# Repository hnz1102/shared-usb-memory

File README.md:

<div align="center">
  <h1><code>SHARED-USB-MEMORY</code></h1>
  
</div>

# Shared USB Memory : USB Memory with One-touch Switching Between Two Device Connections

https://github.com/hnz1102/shared-usb-memory/assets/111413646/2c444520-a98f-45e1-a0ac-f0b2667a8621

This memory provides convenient and quick-to-switch connections between two host devices such as PCs.

When the network is not available, data is transferred by copying data to and from a USB memory stick or SD card. However, since removing and inserting USB memory sticks and SD cards is a hassle, the Box can be switched at the touch of a button to pass data back and forth.

To use, connect this Box between two PCs with a Type-C cable. The disk will be recognized by the PC connected to the left port. Then, copy data here, and when the red access blinking stops, press the red button. Then the disk will be recognized in the PC of right port and you can retrieve the data. Press the red button again to return the disk to the left PC. In this way, data can be exchanged without having to remove and insert the USB memory stick.

The box can be run on the Windows OS, MacOS, and Linux OS without special drivers.

## Schematic

This Board Schematic and a PCB layout are placed in this directory. 
Schematic data is created by KidCad 7.0.
The PCB was manufuctured by [PCBWay](https://www.pcbway.com/). I could easily order my custom boards to the PCBWay.
Click online order [page](https://www.pcbway.com/QuickOrderOnline.aspx), then clink the "Add Gerber File" button, you can upload the [gerber file](https://github.com/hnz1102/shared-usb-memory/raw/main/shareusbdisk2.kicad_pcb.zip).

When ordering the PCB, the parameters can be almost default values, but "Min hole size" should be 0.25mm and "Immersion gold (ENIG)" should be selected for "Surface finish". The reason for this is that the minimum Via Hole is 0.25mm, and if the eMMC pad is not "Immersion gold (ENIG)", the solder on the pad will be slightly raised and cannot be soldered properly without misalignment.

After assembling the board, It has to configure EEPROMs of the USB Media Controller.

The USB Media Controller has an EEPROM. It is programmed with the parameters by [USBDM tool](https://www.microchip.com/en-us/software-library/usbdm-tool).

- Manufacture String
- Serial Number String

This board has two USB Media Controller. Connect to each of the two respective USB ports and rewrite the information with the USBDM tool. 

# Container

There are STL data for 3D printer in the `stl` directory.

## LICENSE
Hardware Schematic Documents are licensed under CC-BY-SA V4.0.

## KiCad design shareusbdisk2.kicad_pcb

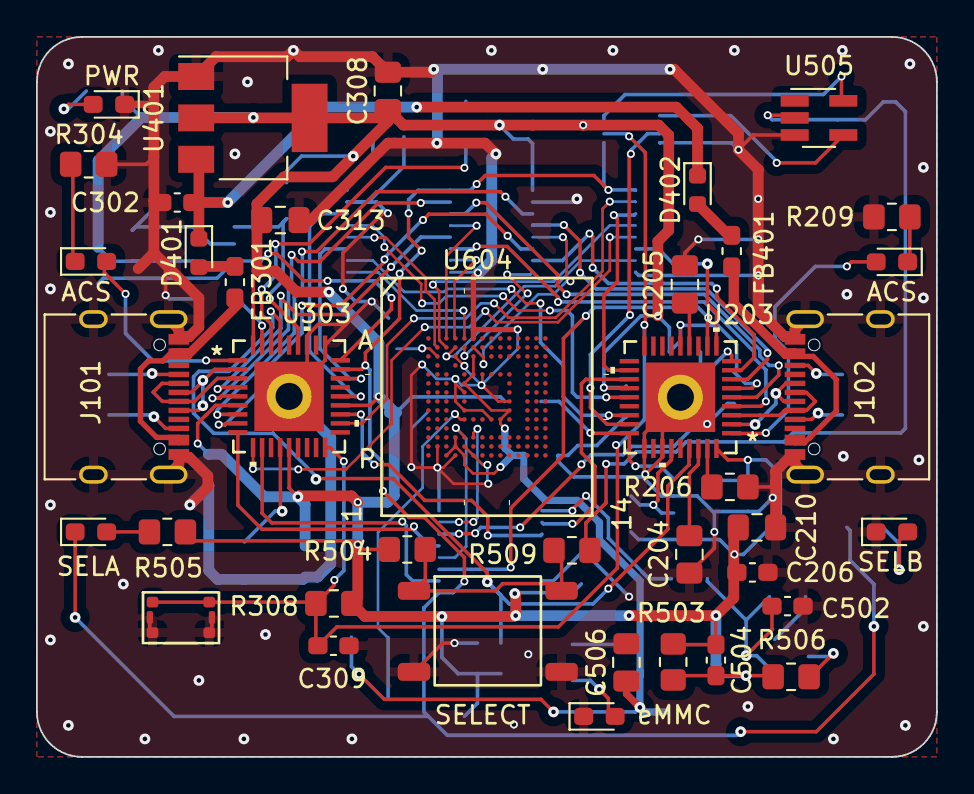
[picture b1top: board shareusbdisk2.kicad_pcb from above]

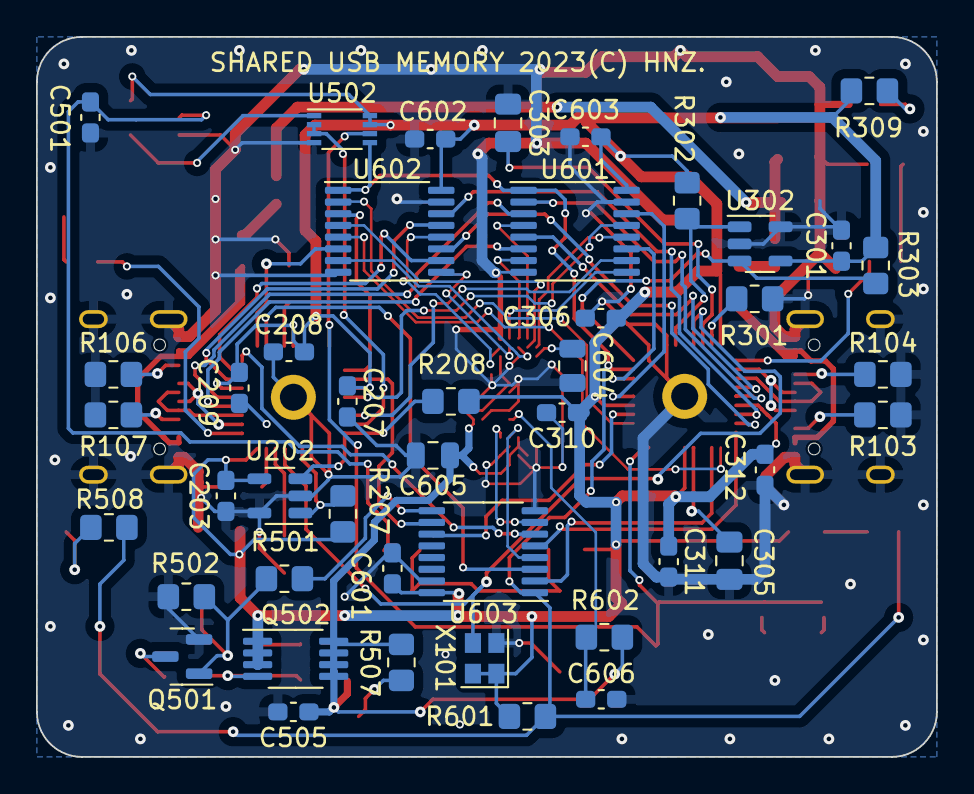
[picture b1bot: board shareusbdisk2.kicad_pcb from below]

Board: 2 copper layers, 50.0 x 40.0 mm, 83 parts (44 on the bottom side), 79 nets.

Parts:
C203, C206, C207, C208, C209, C301, C302, C306, C309, C310, C311, C312, C501, C502, C505, C601, C602, C603, C606: 0.1uF; C_0603_1608Metric_Pad1.08x0.95mm_HandSolder
C204, C205, C303, C305: 1uF; C_0805_2012Metric_Pad1.18x1.45mm_HandSolder
C210, C313: 4.7uF; C_0805_2012Metric_Pad1.18x1.45mm_HandSolder
C308, C506: 10uF; C_0805_2012Metric_Pad1.18x1.45mm_HandSolder
C504: 2.2uF; C_0603_1608Metric_Pad1.08x0.95mm_HandSolder
C604, C605: 1uF; C_0805_2012Metric
D203, D301, D302: LED RED; LED_0603_1608Metric_Pad1.05x0.95mm_HandSolder
D401, D402: CDBU0520-HF; D_0603_1608Metric
D501: eMMC PWR LED RED; LED_0603_1608Metric_Pad1.05x0.95mm_HandSolder
D502: SEL_A; LED_0603_1608Metric_Pad1.05x0.95mm_HandSolder
D503: SEL_B; LED_0603_1608Metric_Pad1.05x0.95mm_HandSolder
FB301, FB401: BK2125HS601-T; L_0603_1608Metric_Pad1.05x0.95mm_HandSolder
J101, J102: USB_C_Receptacle_USB2.0_5077CR; USB_C_5077CR-16-SMC2-BK-TR
Q501: 2N7002K; SOT-23
Q502: IRF7606TRPBF; MSOP-8_3x3mm_P0.65mm
R103, R104, R106, R107: 5.1K; R_0805_2012Metric_Pad1.20x1.40mm_HandSolder
R206, R301: 12K 1%; R_0805_2012Metric_Pad1.20x1.40mm_HandSolder
R207, R208, R302, R303, R308, R502, R503, R504, R601, R602: 10K; R_0805_2012Metric_Pad1.20x1.40mm_HandSolder
R209, R304: 330R; R_0805_2012Metric_Pad1.20x1.40mm_HandSolder
R309, R506, R507, R509: 1K; R_0805_2012Metric_Pad1.20x1.40mm_HandSolder
R501: 2K; R_0805_2012Metric_Pad1.20x1.40mm_HandSolder
R505, R508: 330; R_0805_2012Metric_Pad1.20x1.40mm_HandSolder
SW301: RESET SW; WS-TASV SMT Tact Switch
SW501: TS-06104
U202, U302: AT24C04-STUM; SOT-23-5
U203, U303: USB2244-AEZG-06; QFN36_6X6MC_MCH
U401: LD1117S33TR_SOT223; SOT-223-3_TabPin2
U502: 74LVC2G74; VSSOP-8_2.3x2mm_P0.5mm
U505: 74AHC1G14; SOT-23-5_HandSoldering
U601, U602, U603: TMUX1574PWR; TSSOP-16_4.4x5mm_P0.65mm
U604: EM32VSUKN; EM32VSUKN FPGA153
X101: SG-210STF 24MHz; Oscillator_SMD_SeikoEpson_SG210-4Pin_2.5x2.0mm

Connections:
+3.3V: C203.1, C206.1, C207.1, C208.1, C209.1, C210.1, C301.1, C306.1, C308.1, C310.1, C311.1, C312.1, C313.1, C504.1, C601.1, C602.1, C603.1, Q502.1 (S), Q502.2 (S), Q502.3 (S), R207.1, R208.1, R302.1, R303.1, R308.1, R309.1, R503.1, R504.1, R505.1, R601.1, U202.4 (VCC), U203.6 (VDD33), U203.14 (VDD33), U203.22 (VDD33), U203.36 (VDDA33), U302.4 (VCC), U303.6 (VDD33), U303.14 (VDD33), U303.22 (VDD33), U303.36 (VDDA33), U401.2 (VO), U502.7 (~PRE), U502.8 (VCC), U505.5 (VCC), U601.16 (VDD), U602.16 (VDD), U603.16 (VDD), X101.1 (~ST), X101.4 (Vcc)
+5V: C302.1, D401.1 (K), D402.1 (K), U401.3 (VI)
/MUX/CLK: U603.7 (D2), U604.M6 (CLK)
/MUX/CMD: U603.4 (D1), U604.M5 (CMD)
/MUX/CRD_PWR_A: U303.21 (CRD_PWR), U603.11 (S3A)
/MUX/CRD_PWR_B: U203.21 (CRD_PWR), U603.10 (S3B)
/MUX/D0: U601.4 (D1), U604.A3 (DAT0)
/MUX/D1: U601.7 (D2), U604.A4 (DAT1)
/MUX/D2: U601.9 (D3), U604.A5 (DAT2)
/MUX/D3: U601.12 (D4), U604.B2 (DAT3)
/MUX/D4: U602.4 (D1), U604.B3 (DAT4)
/MUX/D5: U602.7 (D2), U604.B4 (DAT5)
/MUX/D6: U602.9 (D3), U604.B5 (DAT6)
/MUX/D7: U602.12 (D4), U604.B6 (DAT7)
/MUX/MMCDA0: U303.5 (SD_D0), U601.2 (S1A)
/MUX/MMCDA1: U303.4 (SD_D1), U601.5 (S2A)
/MUX/MMCDA2: U303.25 (SD_D2), U601.11 (S3A)
/MUX/MMCDA3: U303.23 (SD_D3), U601.14 (S4A)
/MUX/MMCDA4: U303.20 (SD_D4), U602.2 (S1A)
/MUX/MMCDA5: U303.10 (SD_D5), U602.5 (S2A)
/MUX/MMCDA6: U303.8 (SD_D6), U602.11 (S3A)
/MUX/MMCDA7: U303.7 (SD_D7), U602.14 (S4A)
/MUX/MMCDB0: U203.5 (SD_D0), U601.3 (S1B)
/MUX/MMCDB1: U203.4 (SD_D1), U601.6 (S2B)
/MUX/MMCDB2: U203.25 (SD_D2), U601.10 (S3B)
/MUX/MMCDB3: U203.23 (SD_D3), U601.13 (S4B)
/MUX/MMCDB4: U203.20 (SD_D4), U602.3 (S1B)
/MUX/MMCDB5: U203.10 (SD_D5), U602.6 (S2B)
/MUX/MMCDB6: U203.8 (SD_D6), U602.10 (S3B)
/MUX/MMCDB7: U203.7 (SD_D7), U602.13 (S4B)
/MUX/MMC_CLK_A: U303.9 (SD_CLK), U603.5 (S2A)
/MUX/MMC_CLK_B: U203.9 (SD_CLK), U603.6 (S2B)
/MUX/MMC_CMD_A: U303.11 (SD_CMD), U603.2 (S1A)
/MUX/MMC_CMD_B: U203.11 (SD_CMD), U603.3 (S1B)
/MUX/MMC_PWR: C505.1, C506.1, C605.1, Q502.5 (D), Q502.6 (D), Q502.7 (D), Q502.8 (D), R507.1, R602.1, U604.C6 (VCCQ), U604.E6 (VCC), U604.F5 (VCC), U604.J10 (VCC), U604.K9 (VCC), U604.M4 (VCCQ), U604.N4 (VCCQ), U604.P3 (VCCQ), U604.P5 (VCCQ)
/MUX/MMC_PWR_EN: R501.1, U603.9 (D3)
/MUX/~SELA: D502.1 (K), R508.1, R601.2, U303.26 (SD_NCD), U502.5 (Q), U601.1 (SEL), U602.1 (SEL), U603.1 (SEL)
/SDCARD_READER1/ACS: D203.2 (A), U203.1 (LED)
/SDCARD_READER1/CLK24MHZ: U203.33 (XTAL1(CLKIN)), U303.33 (XTAL1(CLKIN)), X101.3 (OUT)
/SDCARD_READER1/SCL: R207.2, U202.1 (SCL), U203.31 (TXD/SCK)
/SDCARD_READER1/SDA: R208.2, U202.3 (SDA), U203.27 (RXD/SDA)
/SDCARD_READER1/USB+: J102.A6 (D+), J102.B6 (D+), U203.2 (USB+)
/SDCARD_READER1/USB-: J102.A7 (D-), J102.B7 (D-), U203.3 (USB-)
/SDCARD_READER1/~MMC_CD: U203.26 (SD_NCD), U502.2 (D), U502.3 (~Q)
/SDCARD_READER1/~RESET: C309.1, R308.2, SW301.1, SW301.2, U203.18 (RESET_N), U303.18 (RESET_N), U502.6 (~CLR)
/SDCARD_READER2/ACS: D301.2 (A), U303.1 (LED)
/SDCARD_READER2/SCL: R302.2, U302.1 (SCL), U303.31 (TXD/SCK)
/SDCARD_READER2/SDA: R303.2, U302.3 (SDA), U303.27 (RXD/SDA)
/SDCARD_READER2/USB+: J101.A6 (D+), J101.B6 (D+), U303.2 (USB+)
/SDCARD_READER2/USB-: J101.A7 (D-), J101.B7 (D-), U303.3 (USB-)
/USB POWER/USBVDD_5V_A: FB301.1, J101.A4 (VBUS), J101.A9 (VBUS), J101.B4 (VBUS), J101.B9 (VBUS)
/USB POWER/USBVDD_5V_B: FB401.1, J102.A4 (VBUS), J102.A9 (VBUS), J102.B4 (VBUS), J102.B9 (VBUS)
GND: C203.2, C204.2, C205.2, C206.2, C207.2, C208.2, C209.2, C210.2, C301.2, C302.2, C303.2, C305.2, C306.2, C308.2, C309.2, C310.2, C311.2, C312.2, C313.2, C501.2, C502.2, C505.2, C506.2, C601.2, C602.2, C603.2, C604.2, C605.2, C606.2, D302.1 (K), D501.1 (K), D503.1 (K), J101.A1 (GND), J101.A12 (GND), J101.B1 (GND), J101.B12 (GND), J101.S1 (SHIELD), J102.A1 (GND), J102.A12 (GND), J102.B1 (GND), J102.B12 (GND), J102.S1 (SHIELD), Q501.2 (S), R103.2, R104.2, R106.2, R107.2, R206.2, R209.2, R301.2, R304.2, R502.2, SW301.3 (K), SW301.4 (A), SW301.5, SW301.6, SW501.A, SW501.B, U202.2 (GND), U202.5 (WP), U203.28 (TEST), U203.30 (SD_WP), U203.37 (EPAD), U302.2 (GND), U302.5 (WP), U303.28 (TEST), U303.30 (SD_WP), U303.37 (EPAD), U401.1 (GND), U502.4 (GND), U505.3 (GND), U601.8 (GND), U601.15 (~EN), U602.8 (GND), U602.15 (~EN), U603.8 (GND), U603.15 (~EN), U604.A6 (VSS), U604.C4 (VSSQ), U604.E7 (VSS), U604.G5 (VSS), U604.H10 (VSS), U604.J5 (VSS), U604.K8 (VSS), U604.N2 (VSSQ), U604.N5 (VSSQ), U604.P4 (VSSQ), U604.P6 (VSSQ), X101.2 (GND)
unnamed: C501.1, R509.1, U505.2
unnamed: D203.1 (K), R209.1
unnamed: D301.1 (K), R304.1
unnamed: D302.2 (A), R309.2
unnamed: D401.2 (A), FB301.2
unnamed: D402.2 (A), FB401.2
unnamed: D501.2 (A), R507.2
unnamed: D502.2 (A), R505.2
unnamed: D503.2 (A), R508.2
unnamed: J101.A5 (CC1), R104.1
unnamed: J101.B5 (CC2), R103.1
unnamed: J102.A5 (CC1), R107.1
unnamed: J102.B5 (CC2), R106.1
unnamed: Q501.3 (D), R506.1
unnamed: C502.1, Q501.1 (G), R501.2, R502.1
unnamed: C504.2, Q502.4 (G), R503.2, R506.2
unnamed: R504.2, R509.2, SW501.C, SW501.D
unnamed: R206.1, U203.35 (RBIAS)
unnamed: C205.1, U203.13 (VDD18)
unnamed: C204.1, U203.34 (VDD18PLL)
unnamed: R301.1, U303.35 (RBIAS)
unnamed: C305.1, U303.13 (VDD18)
unnamed: C303.1, U303.34 (VDD18PLL)
unnamed: U502.1 (C), U505.4
unnamed: C604.1, U604.C2 (VDDI)
unnamed: C606.1, R602.2, U604.K5 (~RST)

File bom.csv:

Reference,Value,Footprint,Datasheet,digikey,storeURL,Qty
"C206-C209,  C301, C302, C306, C309-C312, C501,  C502,  C505, C601-C603,  C606",0.1uF,Capacitor_SMD:C_0603_1608Metric_Pad1.08x0.95mm_HandSolder,~,311-1824-1-ND,https://www.digikey.com/en/products/detail/yageo/CC0603MRX7R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,19
"C204, C205, C303, C305",1uF,tbctl:C_0805_2012Metric_Pad1.18x1.45mm_HandSolder,~,13-CC0603KPX7R7BB105CT-ND,https://www.digikey.com/en/products/detail/yageo/CC0603KPX7R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,4
"C210, C313",4.7uF,tbctl:C_0805_2012Metric_Pad1.18x1.45mm_HandSolder,~,311-1455-1-ND,https://www.digikey.com/en/products/detail/yageo/CC0603KRX5R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,2
"C308, C506",10uF,Capacitor_SMD:C_0805_2012Metric_Pad1.18x1.45mm_HandSolder,~,311-3494-1-ND,https://www.digikey.com/en/products/detail/yageo/CC0603MRX5R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,2
C504,2.2uF,Capacitor_SMD:C_0603_1608Metric_Pad1.08x0.95mm_HandSolder,~,311-1795-1-ND,https://www.digikey.com/en/products/detail/yageo/CC0603KRX7R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,1
"C604, C605",1uF,Capacitor_SMD:C_0805_2012Metric,~,13-CC0603KPX7R7BB105CT-ND,https://www.digikey.com/en/products/detail/yageo/CC0603KPX7R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,2
"D203, D301, D302",LED RED,tbctl:LED_0603_1608Metric_Pad1.05x0.95mm_HandSolder,~,511-1587-1-ND,https://www.digikey.com/en/products/detail/rohm-semiconducto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,3
"D401, D402",CDBU0520-HF,Diode_SMD:D_0603_1608Metric,https://www.comchiptech.com/admin/files/product/QW-G1012-CDB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,641-2022-1-ND,https://www.digikey.com/en/products/detail/comchip-technolog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,2
D501,eMMC PWR LED RED,tbctl:LED_0603_1608Metric_Pad1.05x0.95mm_HandSolder,~,511-1587-1-ND,https://www.digikey.com/en/products/detail/rohm-semiconducto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,1
D502,SEL_A,tbctl:LED_0603_1608Metric_Pad1.05x0.95mm_HandSolder,~,846-1177-1-ND,https://www.digikey.com/en/products/detail/rohm-semiconducto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,1
D503,SEL_B,tbctl:LED_0603_1608Metric_Pad1.05x0.95mm_HandSolder,~,846-1177-1-ND,https://www.digikey.com/en/products/detail/rohm-semiconducto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,1
"FB301, FB401",BK2125HS601-T,tbctl:L_0603_1608Metric_Pad1.05x0.95mm_HandSolder,~,240-2399-1-ND ,https://www.digikey.com/en/products/detail/laird-signal-inte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,2
"J101, J102",USB_C_Receptacle_USB2.0_5077CR,tbctl:USB_C_5077CR-16-SMC2-BK-TR,https://www.usb.org/sites/default/files/documents/usb_type-c.zip,2073-USB4105-GF-ACT-ND,https://www.digikey.com/en/products/detail/gct/USB4105-GF-A/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,2
Q501,2N7002K,Package_TO_SOT_SMD:SOT-23,https://www.diodes.com/assets/Datasheets/ds30896.pdf,2N7002K-7DICT-ND,https://www.digikey.com/en/products/detail/diodes-incorporat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,1
Q502,IRF7606TRPBF,Package_SO:MSOP-8_3x3mm_P0.65mm,http://www.irf.com/product-info/datasheets/data/irf7606pbf.pdf,IRF7606TRPBFCT-ND,https://www.digikey.com/en/products/detail/infineon-technolo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,1
"R103, R104, R106, R107",5.1K,tbctl:R_0805_2012Metric_Pad1.20x1.40mm_HandSolder,~,13-RC0603JR-1010KLCT-ND,https://www.digikey.com/en/products/detail/yageo/RC0603JR-10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,4
"R206, R301",12K 1%,tbctl:R_0805_2012Metric_Pad1.20x1.40mm_HandSolder,~,311-12.0KHRCT-ND,https://www.digikey.com/en/products/detail/yageo/RC0603FR-07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,2
"R207, R208, R302, R303, R308, R502-R504, R601, R602",10K,tbctl:R_0805_2012Metric_Pad1.20x1.40mm_HandSolder,~,13-RC0603JR-1010KLCT-ND,https://www.digikey.com/en/products/detail/yageo/RC0603JR-10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,10
"R209, R304",330R,tbctl:R_0805_2012Metric_Pad1.20x1.40mm_HandSolder,~,311-330GRCT-ND,https://www.digikey.com/en/products/detail/yageo/RC0603JR-07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,2
"R309, R506, R507, R509",1K,tbctl:R_0805_2012Metric_Pad1.20x1.40mm_HandSolder,~,13-RC0603JR-101KLCT-ND,https://www.digikey.com/en/products/detail/yageo/RC0603JR-10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,4
R501,2K,tbctl:R_0805_2012Metric_Pad1.20x1.40mm_HandSolder,~,311-2.0KGRCT-ND,https://www.digikey.com/en/products/detail/yageo/RC0603JR-07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,1
"R505, R508",330,tbctl:R_0805_2012Metric_Pad1.20x1.40mm_HandSolder,~,13-RC0603JR-101KLCT-ND,https://www.digikey.com/en/products/detail/yageo/RC0603JR-10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,2
SW301,RESET SW,tbctl:WS-TASV SMT Tact Switch,,732-435151014824CT-ND,https://www.digikey.com/en/products/detail/w%C3%BCrth-elektr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,1
SW501,TS-06104,tbctl:TS-06104,,,https://akizukidenshi.com/catalog/g/gP-15969/,1
"U202, U302",AT24C04-STUM,Package_TO_SOT_SMD:SOT-23-5,http://ww1.microchip.com/downloads/en/DeviceDoc/Atmel-8766-S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,AT24C04C-STUM-TCT-ND,https://www.digikey.com/en/products/detail/microchip-technol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,2
"U203, U303",USB2244-AEZG-06,tbctl:QFN36_6X6MC_MCH,USB2244-AEZG-06,USB2244-AEZG-06-ND,https://www.digikey.com/en/products/detail/microchip-technol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,2
U401,LD1117S33TR_SOT223,Package_TO_SOT_SMD:SOT-223-3_TabPin2,http://www.st.com/st-web-ui/static/active/en/resource/techni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,497-1242-1-ND,https://www.digikey.com/en/products/detail/stmicroelectronic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,1
U502,74LVC2G74,Package_SO:VSSOP-8_2.3x2mm_P0.5mm,,TC7W74FKLFCT-ND,https://www.digikey.com/en/products/detail/toshiba-semicondu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,1
U505,74AHC1G14,Package_TO_SOT_SMD:SOT-23-5_HandSoldering,,74AHC1G14W5-7DICT-ND,https://www.digikey.com/en/products/detail/diodes-incorporat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,1
U601-U603,TMUX1574PWR,Package_SO:TSSOP-16_4.4x5mm_P0.65mm,,296-53444-1-ND ,https://www.digikey.com/en/products/detail/texas-instruments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,3
U604,EM32VSUKN,tbctl:EM32VSUKN FPGA153,,3247-EM32VSUKN-BA000-2-ND,https://www.digikey.com/en/products/detail/delkin-devices-in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,1
X101,SG-210STF 24MHz,Oscillator:Oscillator_SMD_SeikoEpson_SG210-4Pin_2.5x2.0mm,https://support.epson.biz/td/api/doc_check.php?mode=dl&lang=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,SER4078CT-ND,https://www.digikey.com/en/products/detail/epson/SG-210STF-2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,1
